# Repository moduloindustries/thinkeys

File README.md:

View this project on [CADLAB.io](https://cadlab.io/project/24445). 

ThinKeys
========
Split ortholinear custom replacement keyboard with TrackPoint for ThinkPad laptops.

Layout can be mapped as desired with QMK.

Other physical layouts will be offered if there is enough demand for them.

Videos
------
- [Playlist (YouTube)](https://www.youtube.com/playlist?list=PLA83yaoqEOKUAF3hhw5IN6eBIaD0fTjDs)

Compatibility
-------------
The first model is for Lenovo ThinkPads T410-T430, T510-T530, W510-W530, and
X220-X230 (including s, i, and t suffixed variants).

Later model support planned for X230s-X270, T431s-T450s/T440(p)-T460(p) and
beyond.

Goals
-----
- [X] TrackPoint
- [X] Split for external/desktop use (connect via USB Type-C)
- [X] Ortholinear
- [ ] ~~RGB LED Backlight (ThinkLight infeasible)~~ No backlight in the first
      version, maybe next time
- [X] USB Connection
- [X] Power Button
- [X] Socketable Pro Micro (or compatible)

Chat
----
Join via Matrix: https://matrix.to/#/!igsJfJkAlUganwyDzE:librem.one?via=librem.one

Join via Discord: https://discord.gg/MA2DBqRyEK

Low Profile Keyboards Discord: https://discord.gg/yhGEvATCFs

Pineapples
----------
Inspiration and some design from https://github.com/saoto28/pineapple60

Older models like xx20/xx30 have a lot more keyboard thickness (height?) than
newer ones like T460s/T470s, so lid closing clearance is not expected be an
issue.

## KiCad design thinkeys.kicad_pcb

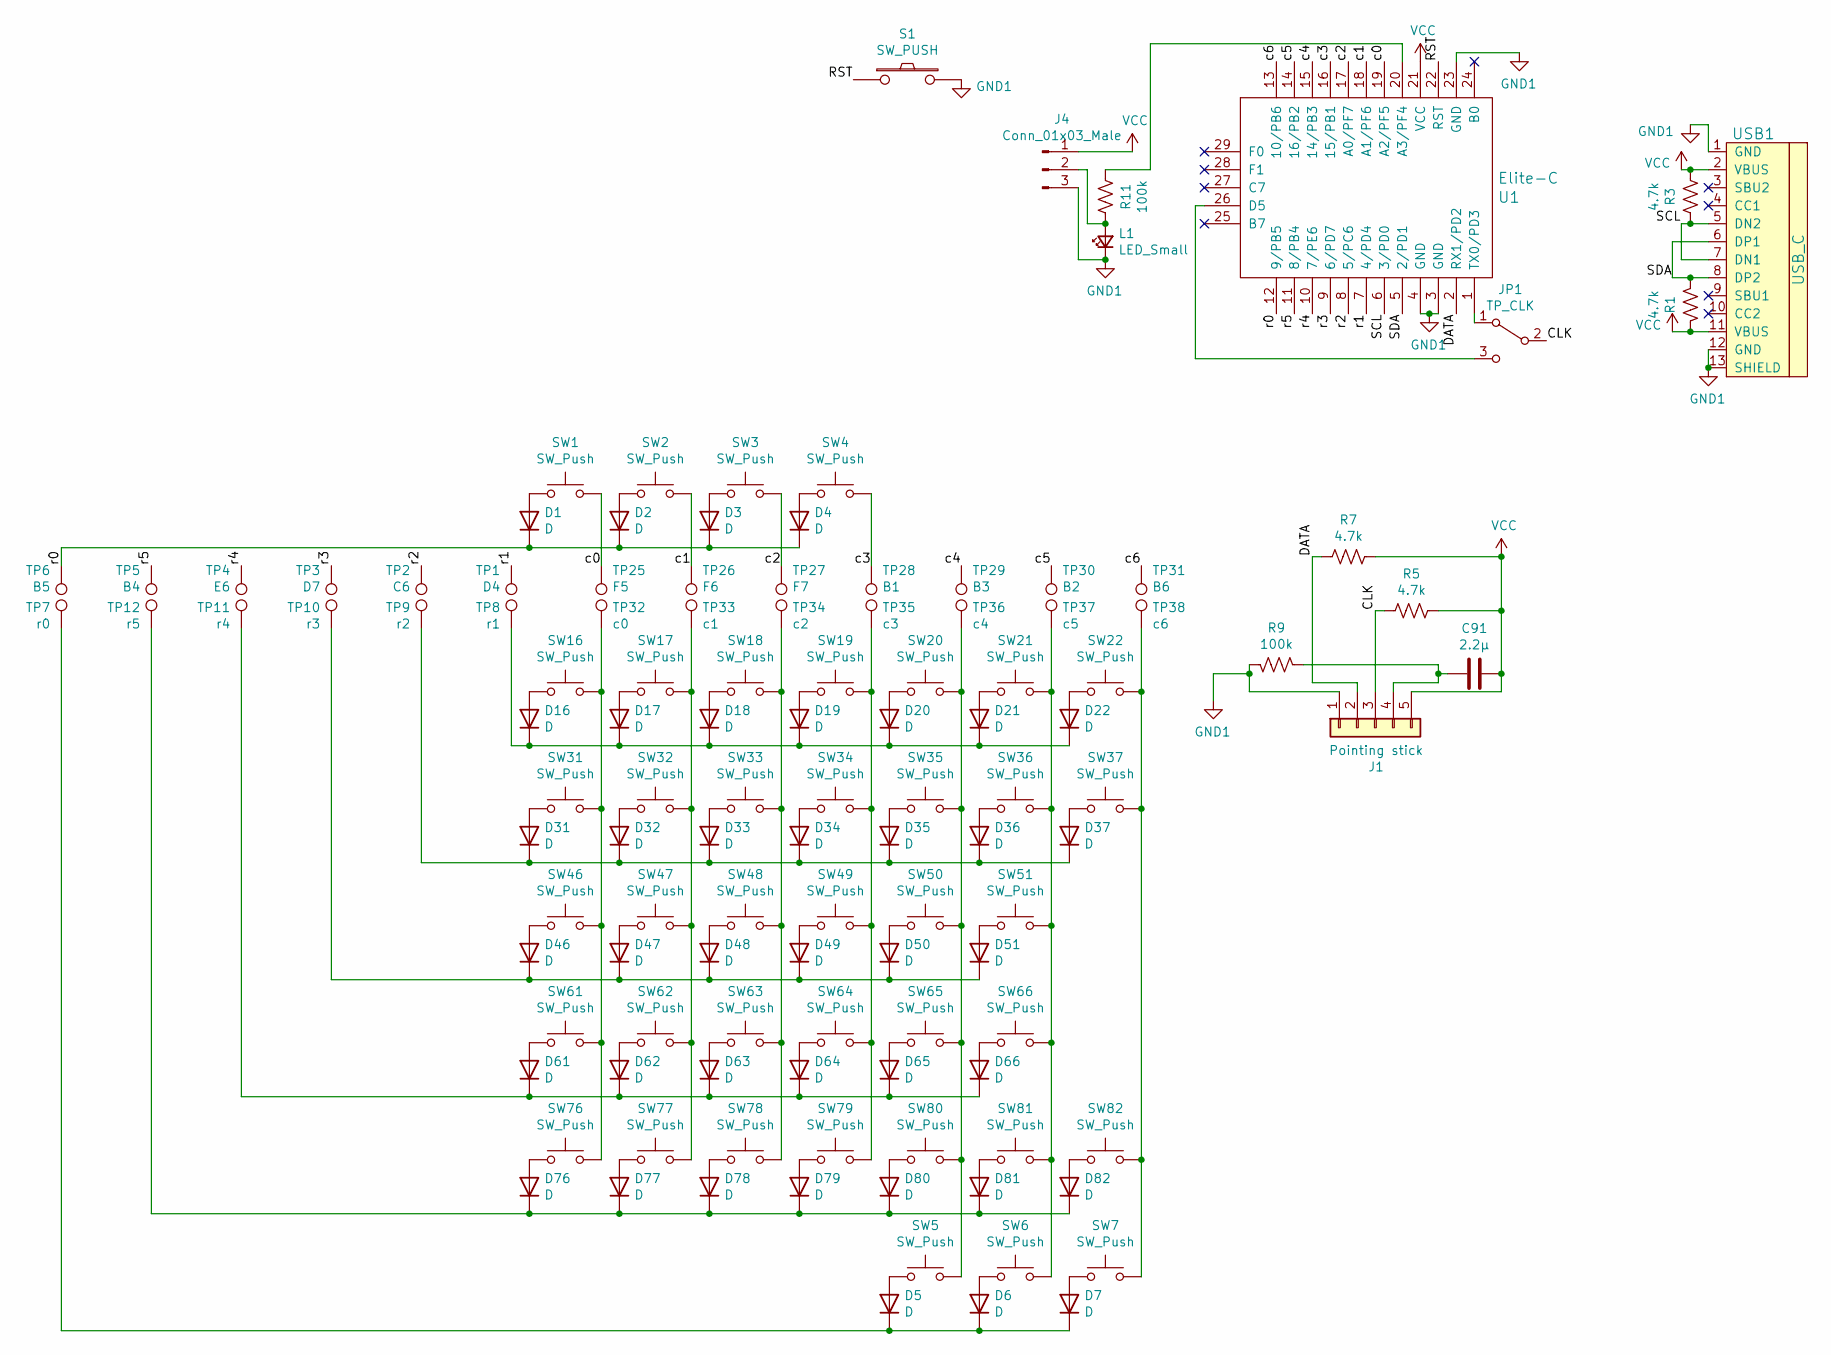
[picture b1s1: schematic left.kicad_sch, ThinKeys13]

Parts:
C91: 2.2µ; C_1206_3216Metric_Pad1.33x1.80mm_HandSolder; LCSC Part C50254
D1, D2, D3, D4, D5, D6, D7, D16, D17, D18, D19, D20, D21, D22, D31, D32, D33, D34, D35, D36, D37, D46, D47, D48, D49, D50, D51, D61, D62, D63, D64, D65, D66, D76, D77, D78, D79, D80, D81, D82: D; D_SOD-123; LCSC Part C64898
J1: Pointing stick; SK8707-01
J4: Conn_01x03_Male; PinHeader_1x03_P2.00mm_Vertical_SMD_Pin1Left
JP1: TP_CLK; SolderJumper-3_P1.3mm_Open_RoundedPad1.0x1.5mm_NumberLabels
L1: LED_Small; LED_0805_2012Metric_Castellated; LCSC Part C72043
R1, R3, R5, R7: 4.7k; R_1206_3216Metric_Pad1.30x1.75mm_HandSolder; LCSC Part C17936
R9: 100k; R_1206_3216Metric_Pad1.30x1.75mm_HandSolder; LCSC Part C17900
R11: 100k; R_1206_3216Metric_Pad1.30x1.75mm_HandSolder; LCSC Part C17936
S1: SW_PUSH; SW_SPST_EVQQ2; LCSC Part C713483
SW1, SW2, SW3, SW4, SW5, SW6, SW7, SW16, SW17, SW18, SW19, SW20, SW21, SW22, SW31, SW32, SW33, SW34, SW35, SW36, SW37, SW46, SW47, SW48, SW49, SW50, SW51, SW61, SW62, SW63, SW64, SW65, SW66, SW76, SW77, SW78, SW79, SW80, SW81, SW82: SW_Push; SW_MX-ALPS-ChocV1_V2-X-PG1280_PCB
TP1: D4; SMDPad_4.0x2.0mm
TP2: C6; SMDPad_4.0x2.0mm
TP3: D7; SMDPad_4.0x2.0mm
TP4: E6; SMDPad_4.0x2.0mm
TP5: B4; SMDPad_4.0x2.0mm
TP6: B5; SMDPad_4.0x2.0mm
TP7: r0; THTPad_4.0x4.0mm_Drill2.0mm
TP8: r1; THTPad_4.0x4.0mm_Drill2.0mm
TP9: r2; THTPad_4.0x4.0mm_Drill2.0mm
TP10: r3; THTPad_4.0x4.0mm_Drill2.0mm
TP11: r4; THTPad_4.0x4.0mm_Drill2.0mm
TP12: r5; THTPad_4.0x4.0mm_Drill2.0mm
TP25: F5; SMDPad_4.0x2.0mm
TP26: F6; SMDPad_4.0x2.0mm
TP27: F7; SMDPad_4.0x2.0mm
TP28: B1; SMDPad_4.0x2.0mm
TP29: B3; SMDPad_4.0x2.0mm
TP30: B2; SMDPad_4.0x2.0mm
TP31: B6; SMDPad_4.0x2.0mm
TP32: c0; THTPad_4.0x4.0mm_Drill2.0mm
TP33: c1; THTPad_4.0x4.0mm_Drill2.0mm
TP34: c2; THTPad_4.0x4.0mm_Drill2.0mm
TP35: c3; THTPad_4.0x4.0mm_Drill2.0mm
TP36: c4; THTPad_4.0x4.0mm_Drill2.0mm
TP37: c5; THTPad_4.0x4.0mm_Drill2.0mm
TP38: c6; THTPad_4.0x4.0mm_Drill2.0mm
U1: Elite-C
USB1: USB_C; HRO-TYPE-C-31-M-12; LCSC Part C165948

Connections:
/left/CLK: J1.3, JP1.2 (B), R5.1
/left/DATA: J1.2, R7.1, U1.2 (RX1/PD2)
/left/RST: S1.1, U1.22 (RST)
/left/SCL: R3.1, U1.6 (3/PD0), USB1.5 (DN2), USB1.7 (DN1)
/left/SDA: R1.1, U1.5 (2/PD1), USB1.6 (DP1), USB1.8 (DP2)
/left/c0: SW1.2, TP25.1, U1.19 (A2/PF5)
/left/c1: SW2.2, TP26.1, U1.18 (A1/PF6)
/left/c2: SW3.2, TP27.1, U1.17 (A0/PF7)
/left/c3: SW4.2, TP28.1, U1.16 (15/PB1)
/left/c4: TP29.1, U1.15 (14/PB3)
/left/c5: TP30.1, U1.14 (16/PB2)
/left/c6: TP31.1, U1.13 (10/PB6)
/left/r0: D1.1 (K), D2.1 (K), D3.1 (K), D4.1 (K), TP6.1, U1.12 (9/PB5)
/left/r1: TP1.1, U1.7 (4/PD4)
/left/r2: TP2.1, U1.8 (5/PC6)
/left/r3: TP3.1, U1.9 (6/PD7)
/left/r4: TP4.1, U1.10 (7/PE6)
/left/r5: TP5.1, U1.11 (8/PB4)
GND1: J1.1, J4.3, L1.1 (K), R9.2, S1.2, U1.3 (GND), U1.4 (GND), U1.23 (GND), USB1.1 (GND), USB1.12 (GND), USB1.13 (SHIELD)
unnamed: C91.1, J1.4, R9.1
unnamed: D1.2 (A), SW1.1
unnamed: D2.2 (A), SW2.1
unnamed: D3.2 (A), SW3.1
unnamed: D4.2 (A), SW4.1
unnamed: D5.1 (K), D6.1 (K), D7.1 (K), TP7.1
unnamed: D5.2 (A), SW5.1
unnamed: D6.2 (A), SW6.1
unnamed: D7.2 (A), SW7.1
unnamed: D16.1 (K), D17.1 (K), D18.1 (K), D19.1 (K), D20.1 (K), D21.1 (K), D22.1 (K), TP8.1
unnamed: D16.2 (A), SW16.1
unnamed: D17.2 (A), SW17.1
unnamed: D18.2 (A), SW18.1
unnamed: D19.2 (A), SW19.1
unnamed: D20.2 (A), SW20.1
unnamed: D21.2 (A), SW21.1
unnamed: D22.2 (A), SW22.1
unnamed: D31.1 (K), D32.1 (K), D33.1 (K), D34.1 (K), D35.1 (K), D36.1 (K), D37.1 (K), TP9.1
unnamed: D31.2 (A), SW31.1
unnamed: D32.2 (A), SW32.1
unnamed: D33.2 (A), SW33.1
unnamed: D34.2 (A), SW34.1
unnamed: D35.2 (A), SW35.1
unnamed: D36.2 (A), SW36.1
unnamed: D37.2 (A), SW37.1
unnamed: D46.1 (K), D47.1 (K), D48.1 (K), D49.1 (K), D50.1 (K), D51.1 (K), TP10.1
unnamed: D46.2 (A), SW46.1
unnamed: D47.2 (A), SW47.1
unnamed: D48.2 (A), SW48.1
unnamed: D49.2 (A), SW49.1
unnamed: D50.2 (A), SW50.1
unnamed: D51.2 (A), SW51.1
unnamed: D61.1 (K), D62.1 (K), D63.1 (K), D64.1 (K), D65.1 (K), D66.1 (K), TP11.1
unnamed: D61.2 (A), SW61.1
unnamed: D62.2 (A), SW62.1
unnamed: D63.2 (A), SW63.1
unnamed: D64.2 (A), SW64.1
unnamed: D65.2 (A), SW65.1
unnamed: D66.2 (A), SW66.1
unnamed: D76.1 (K), D77.1 (K), D78.1 (K), D79.1 (K), D80.1 (K), D81.1 (K), D82.1 (K), TP12.1
unnamed: D76.2 (A), SW76.1
unnamed: D77.2 (A), SW77.1
unnamed: D78.2 (A), SW78.1
unnamed: D79.2 (A), SW79.1
unnamed: D80.2 (A), SW80.1
unnamed: D81.2 (A), SW81.1
unnamed: D82.2 (A), SW82.1
unnamed: J4.2, L1.2 (A), R11.2
unnamed: JP1.1 (A), U1.1 (TX0/PD3)
unnamed: JP1.3 (C), U1.26 (D5)
unnamed: R11.1, U1.20 (A3/PF4)
unnamed: SW16.2, SW31.2, SW46.2, SW61.2, SW76.2, TP32.1
unnamed: SW17.2, SW32.2, SW47.2, SW62.2, SW77.2, TP33.1
unnamed: SW18.2, SW33.2, SW48.2, SW63.2, SW78.2, TP34.1
unnamed: SW19.2, SW34.2, SW49.2, SW64.2, SW79.2, TP35.1
unnamed: SW5.2, SW20.2, SW35.2, SW50.2, SW65.2, SW80.2, TP36.1
unnamed: SW6.2, SW21.2, SW36.2, SW51.2, SW66.2, SW81.2, TP37.1
unnamed: SW7.2, SW22.2, SW37.2, SW82.2, TP38.1
VCC: C91.2, J1.5, J4.1, R1.2, R3.2, R5.2, R7.2, U1.21 (VCC), USB1.2 (VBUS), USB1.11 (VBUS)

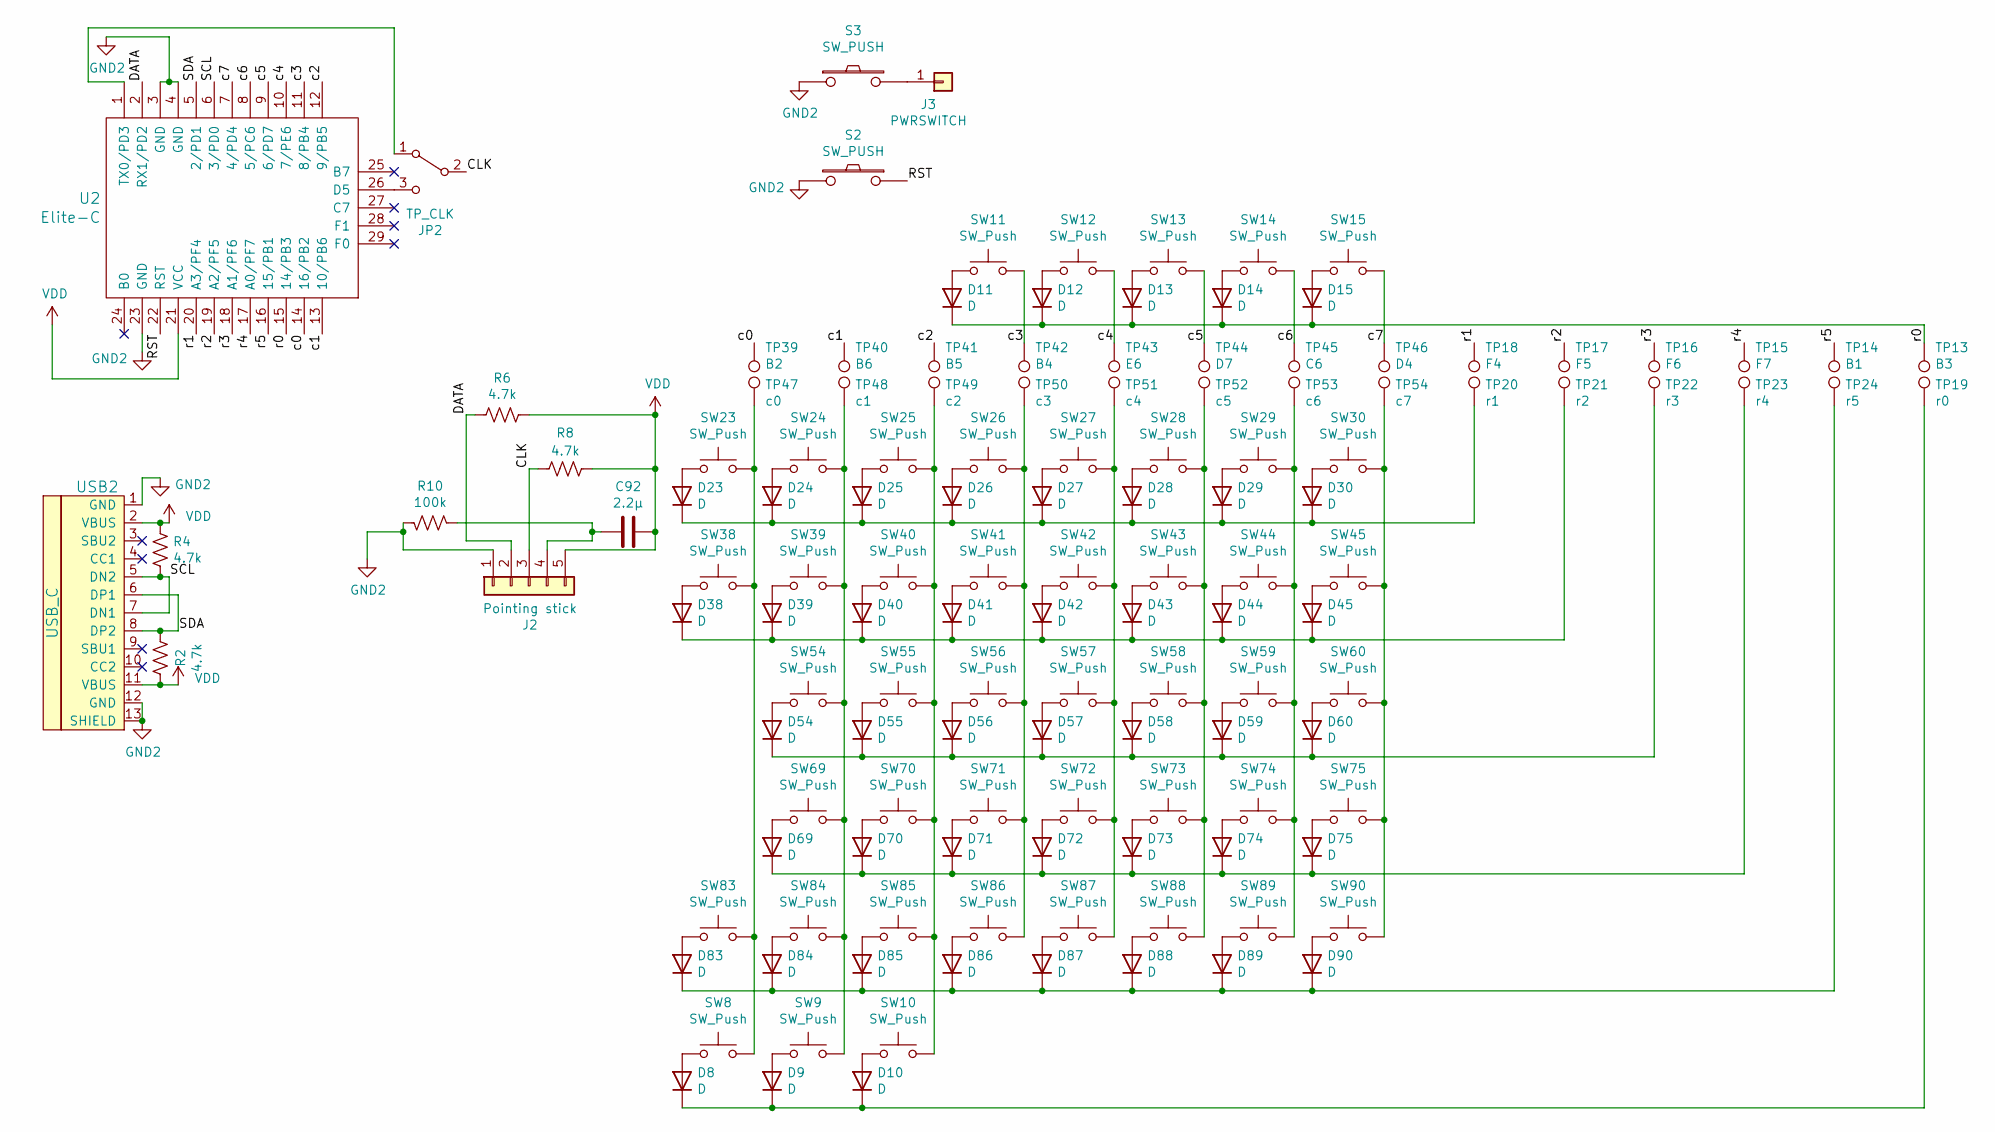
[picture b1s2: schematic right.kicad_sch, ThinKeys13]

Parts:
C92: 2.2µ; C_1206_3216Metric_Pad1.33x1.80mm_HandSolder; LCSC Part C50254
D8, D9, D10, D11, D12, D13, D14, D15, D23, D24, D25, D26, D27, D28, D29, D30, D38, D39, D40, D41, D42, D43, D44, D45, D54, D55, D56, D57, D58, D59, D60, D69, D70, D71, D72, D73, D74, D75, D83, D84, D85, D86, D87, D88, D89, D90: D; D_SOD-123; LCSC Part C64898
J2: Pointing stick; SK8707-01
J3: PWRSWITCH; PinHeader_1x01_P2.54mm_Horizontal
JP2: TP_CLK; SolderJumper-3_P1.3mm_Open_RoundedPad1.0x1.5mm_NumberLabels
R2, R4, R6, R8: 4.7k; R_1206_3216Metric_Pad1.30x1.75mm_HandSolder; LCSC Part C17936
R10: 100k; R_1206_3216Metric_Pad1.30x1.75mm_HandSolder; LCSC Part C17900
S2, S3: SW_PUSH; SW_SPST_EVQQ2; LCSC Part C713483
SW8, SW9, SW10, SW11, SW12, SW13, SW14, SW15, SW23, SW24, SW25, SW26, SW27, SW28, SW29, SW30, SW38, SW39, SW40, SW41, SW42, SW43, SW44, SW45, SW54, SW55, SW56, SW57, SW58, SW59, SW60, SW69, SW70, SW71, SW72, SW73, SW74, SW75, SW83, SW84, SW85, SW86, SW87, SW88, SW89, SW90: SW_Push; SW_MX-ALPS-ChocV1_V2-X-PG1280_PCB
TP13: B3; SMDPad_4.0x2.0mm
TP14: B1; SMDPad_4.0x2.0mm
TP15: F7; SMDPad_4.0x2.0mm
TP16: F6; SMDPad_4.0x2.0mm
TP17: F5; SMDPad_4.0x2.0mm
TP18: F4; SMDPad_4.0x2.0mm
TP19: r0; THTPad_4.0x4.0mm_Drill2.0mm
TP20: r1; THTPad_4.0x4.0mm_Drill2.0mm
TP21: r2; THTPad_4.0x4.0mm_Drill2.0mm
TP22: r3; THTPad_4.0x4.0mm_Drill2.0mm
TP23: r4; THTPad_4.0x4.0mm_Drill2.0mm
TP24: r5; THTPad_4.0x4.0mm_Drill2.0mm
TP39: B2; SMDPad_4.0x2.0mm
TP40: B6; SMDPad_4.0x2.0mm
TP41: B5; SMDPad_4.0x2.0mm
TP42: B4; SMDPad_4.0x2.0mm
TP43: E6; SMDPad_4.0x2.0mm
TP44: D7; SMDPad_4.0x2.0mm
TP45: C6; SMDPad_4.0x2.0mm
TP46: D4; SMDPad_4.0x2.0mm
TP47: c0; THTPad_4.0x4.0mm_Drill2.0mm
TP48: c1; THTPad_4.0x4.0mm_Drill2.0mm
TP49: c2; THTPad_4.0x4.0mm_Drill2.0mm
TP50: c3; THTPad_4.0x4.0mm_Drill2.0mm
TP51: c4; THTPad_4.0x4.0mm_Drill2.0mm
TP52: c5; THTPad_4.0x4.0mm_Drill2.0mm
TP53: c6; THTPad_4.0x4.0mm_Drill2.0mm
TP54: c7; THTPad_4.0x4.0mm_Drill2.0mm
U2: Elite-C
USB2: USB_C; HRO-TYPE-C-31-M-12; LCSC Part C165948

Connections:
/right/CLK: J2.3, JP2.2 (B), R8.1
/right/DATA: J2.2, R6.1, U2.2 (RX1/PD2)
/right/RST: S2.1, U2.22 (RST)
/right/SCL: R4.1, U2.6 (3/PD0), USB2.5 (DN2), USB2.7 (DN1)
/right/SDA: R2.1, U2.5 (2/PD1), USB2.6 (DP1), USB2.8 (DP2)
/right/c0: TP39.1, U2.14 (16/PB2)
/right/c1: TP40.1, U2.13 (10/PB6)
/right/c2: TP41.1, U2.12 (9/PB5)
/right/c3: SW11.2, TP42.1, U2.11 (8/PB4)
/right/c4: SW12.2, TP43.1, U2.10 (7/PE6)
/right/c5: SW13.2, TP44.1, U2.9 (6/PD7)
/right/c6: SW14.2, TP45.1, U2.8 (5/PC6)
/right/c7: SW15.2, TP46.1, U2.7 (4/PD4)
/right/r0: D11.1 (K), D12.1 (K), D13.1 (K), D14.1 (K), D15.1 (K), TP13.1, U2.15 (14/PB3)
/right/r1: TP18.1, U2.20 (A3/PF4)
/right/r2: TP17.1, U2.19 (A2/PF5)
/right/r3: TP16.1, U2.18 (A1/PF6)
/right/r4: TP15.1, U2.17 (A0/PF7)
/right/r5: TP14.1, U2.16 (15/PB1)
GND2: J2.1, R10.2, S2.2, S3.1, U2.3 (GND), U2.4 (GND), U2.23 (GND), USB2.1 (GND), USB2.12 (GND), USB2.13 (SHIELD)
unnamed: C92.1, J2.4, R10.1
unnamed: D8.2 (A), SW8.1
unnamed: D9.2 (A), SW9.1
unnamed: D8.1 (K), D9.1 (K), D10.1 (K), TP19.1
unnamed: D10.2 (A), SW10.1
unnamed: D11.2 (A), SW11.1
unnamed: D12.2 (A), SW12.1
unnamed: D13.2 (A), SW13.1
unnamed: D14.2 (A), SW14.1
unnamed: D15.2 (A), SW15.1
unnamed: D23.1 (K), D24.1 (K), D25.1 (K), D26.1 (K), D27.1 (K), D28.1 (K), D29.1 (K), D30.1 (K), TP20.1
unnamed: D23.2 (A), SW23.1
unnamed: D24.2 (A), SW24.1
unnamed: D25.2 (A), SW25.1
unnamed: D26.2 (A), SW26.1
unnamed: D27.2 (A), SW27.1
unnamed: D28.2 (A), SW28.1
unnamed: D29.2 (A), SW29.1
unnamed: D30.2 (A), SW30.1
unnamed: D38.1 (K), D39.1 (K), D40.1 (K), D41.1 (K), D42.1 (K), D43.1 (K), D44.1 (K), D45.1 (K), TP21.1
unnamed: D38.2 (A), SW38.1
unnamed: D39.2 (A), SW39.1
unnamed: D40.2 (A), SW40.1
unnamed: D41.2 (A), SW41.1
unnamed: D42.2 (A), SW42.1
unnamed: D43.2 (A), SW43.1
unnamed: D44.2 (A), SW44.1
unnamed: D45.2 (A), SW45.1
unnamed: D54.1 (K), D55.1 (K), D56.1 (K), D57.1 (K), D58.1 (K), D59.1 (K), D60.1 (K), TP22.1
unnamed: D54.2 (A), SW54.1
unnamed: D55.2 (A), SW55.1
unnamed: D56.2 (A), SW56.1
unnamed: D57.2 (A), SW57.1
unnamed: D58.2 (A), SW58.1
unnamed: D59.2 (A), SW59.1
unnamed: D60.2 (A), SW60.1
unnamed: D69.1 (K), D70.1 (K), D71.1 (K), D72.1 (K), D73.1 (K), D74.1 (K), D75.1 (K), TP23.1
unnamed: D69.2 (A), SW69.1
unnamed: D70.2 (A), SW70.1
unnamed: D71.2 (A), SW71.1
unnamed: D72.2 (A), SW72.1
unnamed: D73.2 (A), SW73.1
unnamed: D74.2 (A), SW74.1
unnamed: D75.2 (A), SW75.1
unnamed: D83.1 (K), D84.1 (K), D85.1 (K), D86.1 (K), D87.1 (K), D88.1 (K), D89.1 (K), D90.1 (K), TP24.1
unnamed: D83.2 (A), SW83.1
unnamed: D84.2 (A), SW84.1
unnamed: D85.2 (A), SW85.1
unnamed: D86.2 (A), SW86.1
unnamed: D87.2 (A), SW87.1
unnamed: D88.2 (A), SW88.1
unnamed: D89.2 (A), SW89.1
unnamed: D90.2 (A), SW90.1
unnamed: J3.1, S3.2
unnamed: JP2.1 (A), U2.1 (TX0/PD3)
unnamed: JP2.3 (C), U2.26 (D5)
unnamed: SW10.2, SW25.2, SW40.2, SW55.2, SW70.2, SW85.2, TP49.1
unnamed: SW8.2, SW23.2, SW38.2, SW83.2, TP47.1
unnamed: SW9.2, SW24.2, SW39.2, SW54.2, SW69.2, SW84.2, TP48.1
unnamed: SW26.2, SW41.2, SW56.2, SW71.2, SW86.2, TP50.1
unnamed: SW27.2, SW42.2, SW57.2, SW72.2, SW87.2, TP51.1
unnamed: SW28.2, SW43.2, SW58.2, SW73.2, SW88.2, TP52.1
unnamed: SW29.2, SW44.2, SW59.2, SW74.2, SW89.2, TP53.1
unnamed: SW30.2, SW45.2, SW60.2, SW75.2, SW90.2, TP54.1
VDD: C92.2, J2.5, R2.2, R4.2, R6.2, R8.2, U2.21 (VCC), USB2.2 (VBUS), USB2.11 (VBUS)

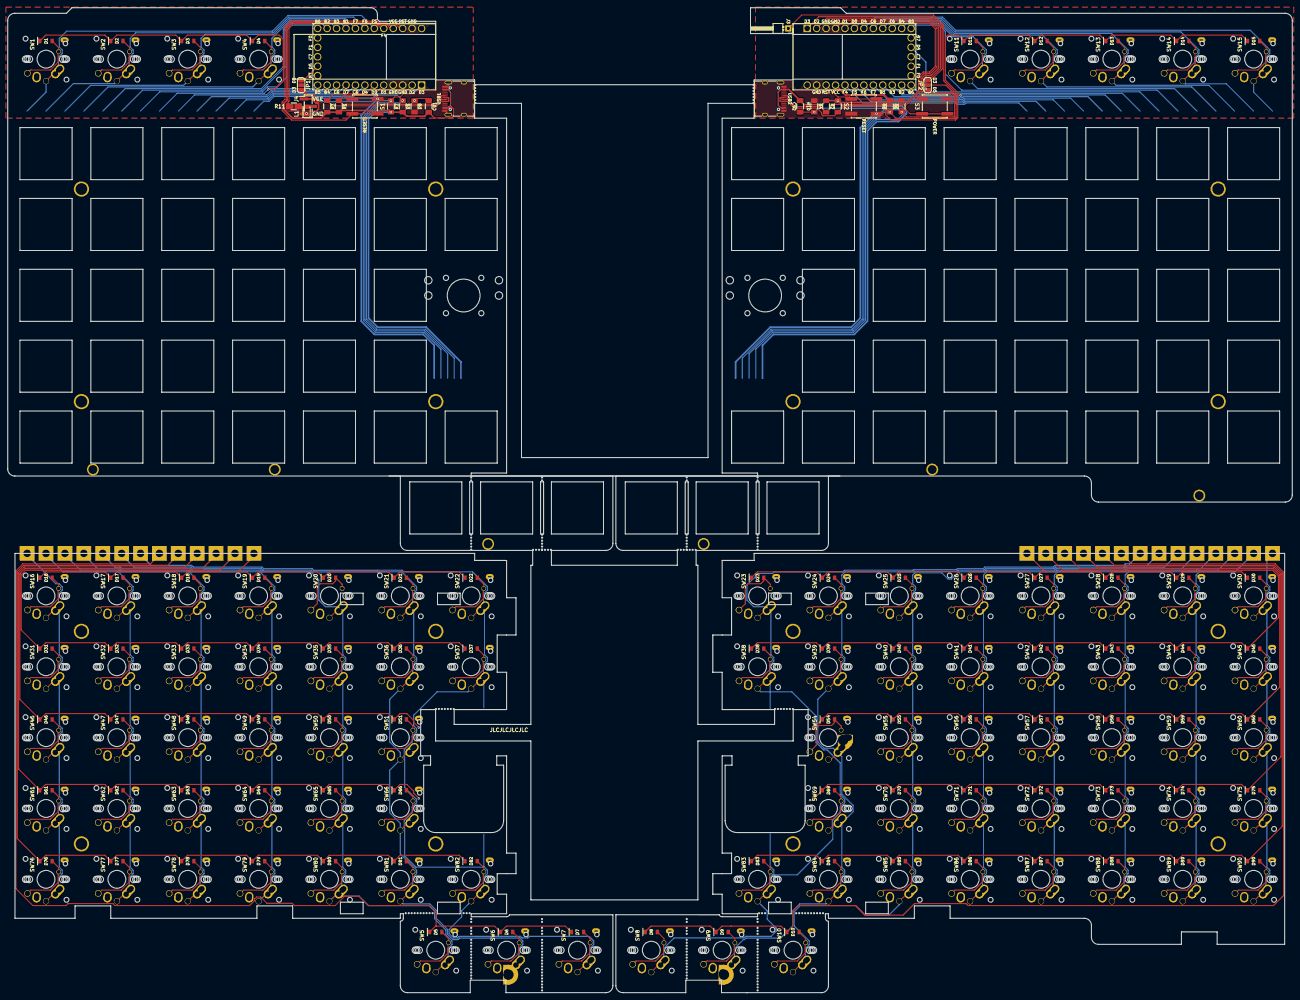
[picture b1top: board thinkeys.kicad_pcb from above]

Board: 2 copper layers, 345.1 x 264.6 mm, 269 parts (0 on the bottom side), 163 nets.

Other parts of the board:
Ref**: Val**; MountingHole_3.2mm
Ref**#2, Ref**#3, Ref**#4, Ref**#5, Ref**#6, Ref**#7, Ref**#8, Ref**#9, Ref**#10, Ref**#11, Ref**#12, Ref**#13, Ref**#14, Ref**#15, Ref**#16: Val**; MountingHole_3.2mm

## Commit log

2021-02-01 number rows
2021-02-01 number cols
2021-02-01 number switches/diodes
2021-02-02 right side
2021-02-02 number right side
2021-02-02 annotate right side
2021-02-03 annotate schematic, add documentation
2021-02-03 fix docs
2021-02-03 resolve #1
2021-02-04 add left side & trrs connection to schematic
2021-02-04 fix row numbering for split
2021-02-04 update documentation
2021-02-06 switch pro micro to use keebio lib; rm unused libs
2021-02-06 fix annotations and footprint assignments
2021-02-06 rotate and center switch footprints; remove cache
2021-02-06 make/use own library for TRRS
2021-02-07 center footprint; isolate mouse buttons; init pcb
2021-02-07 lower diodes
2021-02-07 reduce trrs diameter to 9.779mm
2021-02-08 fix top clearance
2021-02-08 add pointing stick, and some values, to schematic
2021-02-09 harmonize schematic; add library footprint
2021-02-10 add micro switch for pwrswitch, & placement
2021-02-10 make PG1353, PG1442 footprints & merge them in
2021-02-10 add proper spacing for trackpoint buttons
2021-02-11 rm 0.25 silk & redundant footprint pads
2021-02-20 split schematic, add rgb leds, use elite-c pins
2021-02-21 connect gnd's, assign footprints, move right rgb
2021-02-21 add title metadata & page format
2021-02-28 clean up
2021-03-01 set/change footprints, add usb-c, align components
2021-03-01 route main traces
2021-03-01 flip resistors in order, place no connection flags
2021-03-01 update resistors numbers
2021-03-01 align to (0,0)
2021-03-01 revise resistor/capacitor footprints
2021-03-01 clean up labeling
2021-03-02 reroute columns, fix/place leds, fix positions
2021-03-03 add 0.215 mm track width
2021-03-06 improve alignment of elements
2021-03-10 add reset buttons
2021-03-10 add ssd1306 oled display library
2021-03-10 move component libraries
2021-03-10 remove trrs
2021-03-11 move to double pcb design
2021-03-11 put edge cuts and new footprint positions
2021-03-11 use correct ground symbol on right side usb-c
2021-03-11 re-add missing diode 76
2021-03-12 match edge cuts
2021-03-20 caps to leds; route most traces; castellate rows
    also:
    - reassign pins
    - align components
    - switch to new trackpoint footprint
2021-03-20 rm rgb backlight led, castellate columns
2021-03-22 pcb: new footprints & traces
2021-03-27 new dimensions
2021-03-28 panelize alvaro
2021-05-09 more panelization to prepare for prototype
2021-05-09 shift logo/info, comply w/ min slot width for fab
2021-05-09 README.md: update info and images
2021-06-04 unpanelize, fix left vcc zone/right hole, rm slots
2021-06-04 new trackpoint footprint, silk around holes, chocs
2021-06-05 pcb: fix trackpoint tongue and groove dimensions
2021-06-07 pcb: sw54: reinstate choc/mx, x holes, smd spacer
2021-06-07 pcb: shrink mcu cutout to 30x12 mm (301230 batt)
2021-06-08 pcb: don't protrude edge cuts by 0.15mm in middle
2021-06-08 pcb: fix right side trackpoint tongue/groove width
2021-06-08 pcb: make mid trackpoint button slot 0.8mm/fix pos
2021-06-08 pcb: raise outermost trackpoint buttons breakaway
2021-06-08 pcb: fix right side mcu front label b5 orientation
2021-06-08 pcb: introduce rounded slot corners/more top slots
2021-06-08 minimum trace to 0.15mm, left side top B.Cu GND
2021-06-09 pcb: shrink power button pin header through hole
2021-06-10 pcb: fix trackpoint buttons size
2021-06-10 pcb: corner rounding 0.95/0 mm to 1.9 mm
2021-06-10 pcb: fix arrow cluster area size
2021-06-10 pcb: fix minutiae
2021-06-11 Backlink to CADLAB.io has been added.
2021-06-12 pcb: connect top row to mcu/update sch footprints
2021-06-12 pcb: dimensional update
2021-06-12 pcb: update bottom mounting holes/convert to smd
2021-06-12 sch: make it look more like the boardview
2021-06-14 sch: correct oled vcc reference
2021-06-14 switch to new footprints for switches/trackpoints
2021-06-15 pcb: make j3 power button header pin smaller
2021-06-17 oled btfo
2021-06-17 switch to matching flush top pad for bottom hole
2021-06-18 pcb: fix split connection usb location
2021-06-20 redo top positions, routing & footprints
2021-06-22 pcb: finish routing new top area
2021-06-23 pcb: add magnetic tenting kit support
2021-06-23 move trackpoint
2021-06-23 fix left side row pin positions
2021-06-24 pcb: update fill & fix left side jumper label
2021-06-27 make changes for bom output
2021-06-29 pcb: new tab footprint
2021-06-29 pcb: hole update: new mousebites, plate mountholes
2021-07-03 pcb: update switch footprint, prune copper fills
2021-07-03 pcb: remove labels troublesome for panelizing time
2021-07-03 pcb: flip right side labels for panelization
2021-07-03 update castellated label text
2021-07-03 pcb: add symbols
2021-07-03 update title block parameters
2021-07-05 switch to 1206 compoments and add lcsc part number
2021-07-05 pcb: label jumpers as JP**
2021-07-05 add led
2021-07-05 pcb: fix text and footprint location
2021-07-05 prevent text issues, new footprints/3dmodels
2021-07-06 fp-lib: remove unused library
2021-07-09 update footprints/3dmodels
2021-07-09 pcb: extend usb port, adjust copper to match
2021-07-09 move push button references to S**, text to side
2021-07-09 pcb: add Elite-C/Alvaro 3d model
2021-07-10 pcb: add RESET/POWER label
2021-08-16 preparing for production
    - flip right side boards upside down
    - move right side towards the lest
    - move bottom towards the top
    - add mouse bites and rails
    - new detachable tabs implementation
    - move logos
2021-08-16 ground pad, led resistor, PTH screw mount holes
2021-08-21 fix bottom piece usb area cutouts to match the top
2021-09-29 pcb: add eco1.user lines for export to svg cutouts
2021-09-29 pcb: flip right side labels: face more toward user
2021-10-01 pcb: shrink jumper hole size, make it more square
2021-10-06 pcb: add cutout lines for smd spacers
2021-12-17 R11: 4.7 kΩ to 100 kΩ
2021-12-20 pcb: update logo to be bold
2021-12-23 pcb: use updated pointing stick footprints
2021-12-23 pcb: switch to cardioid style castellated landing
2021-12-24 pcb: tab screw M1 to M1.6
2021-12-24 pcb: mounting hole: hide txt/shrink hole 3.2->3.15
2022-01-12 pcb: kicad 6
2022-01-20 pcb: add stackup info
2022-01-20 pcb: jlcpcb pad_to_mask_clearance 0.05
2022-01-29 pcb: new footprints
2022-02-03 sch: kicad 6
2022-02-03 make changes for higher mcu position/potential bat
2022-03-08 spacer: init pcb, kikit panelizer Makefile
2022-03-21 pcb: update footprints, fix panelization cuts
2022-03-21 pcb: move bottom right up, repanelize simply, jlc
2022-03-21 pcb: nice!nano battery terminal wire holes
2022-05-05 pcb: restore right side up panelization
2022-05-05 pcb: add tabs between halves
2022-05-06 pcb: update MX_cutout/SW footprints
2022-05-24 pcb: fix top middle cutout
2022-05-24 pcb: reduce overall width from 287.8mm to 287.5mm
2022-05-24 pcb: breakaway tab arm clear hole by 2mm: jlc spec
2022-05-25 pcb: narrow trackpoint buttons, connect parts
2022-05-25 pcb: left side F4 label, more track-edge clearance
2022-06-08 pcb: mask over castellated pads
2022-06-08 pcb: SK8707-01: label pads
2022-06-09 pcb: make space for rubber
2022-06-10 pcb: extra keys over trackpoint hack
2022-06-11 pcb: redo branding: variables, move to underside
2022-06-14 pcb: enlarge slots to 4mm
2022-06-14 pcb: add jlc specify order number location text
2022-06-14 pcb: date to 2022-06-14
2022-06-17 spacer: height to 3.1mm
2022-07-13 pcb: overall width to 287.5mm
2022-08-03 pcb: bottom/lower jigsaw
2022-08-03 pcb: bottom/upper jigsaw
2022-08-03 pcb: convert joint between top/bottom to v-score
2022-08-24 pcb: total width to 287.3mm
2022-08-31 pcb: move led labels
2022-08-31 pcb: enlarge extra switch pads
2022-08-31 pcb: width revert to 287.8 mm
2022-08-31 pcb: date to 2022-08-31
2022-09-09 spacer: mask over pads
2022-09-09 pcb: widen usb cable housing allowance (12->12.47)
2022-09-11 bump date to 2022-09-11
2022-09-21 Revert "pcb: convert joint between top/bottom to v-score"
    This reverts commit c1ad268ccf8d00d990148b393a468e0298c2c4ef.
2022-09-22 pcb: wide top v-cut for production (less fragile)
2022-09-23 pcb: top: more/symmetric mouse bite holes
2022-09-23 pcb: top: add helper lines for breakaway keys
2022-09-29 pcb: move v-cut text to avoid appearing when fab'd
